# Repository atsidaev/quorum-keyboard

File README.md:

# Мини-клавиатура для Кворум-128

Пленка в клавиатуре Кворума-128 не очень прочна и много у кого уже умерла. На правах костыля можно заменить такую клавиатуру
на текстолитовый суррогат. Для установки требуется выпаять оргинальные разъемы и заменить их на штыри PLS.

# Mini-keyboard for Quorum-128 computer (Russian clone of ZX Spectrum)

Quorum-128 keyboard film is not very durable. But despite the Sinclair ZX Spectrum film, it cannot be simply bought on eBay.
So more radical solution is required.

This repo contains KiCad sources for very small repalcement keyboard. To install it one should replace film connector with
PLS pins.

## Explanation and soldering video

## Photos

## Gerbers

See Releases tab. 
[Latest version](https://github.com/atsidaev/quorum_keyboard/releases/download/v1.0/quorum-keyboard.zip)

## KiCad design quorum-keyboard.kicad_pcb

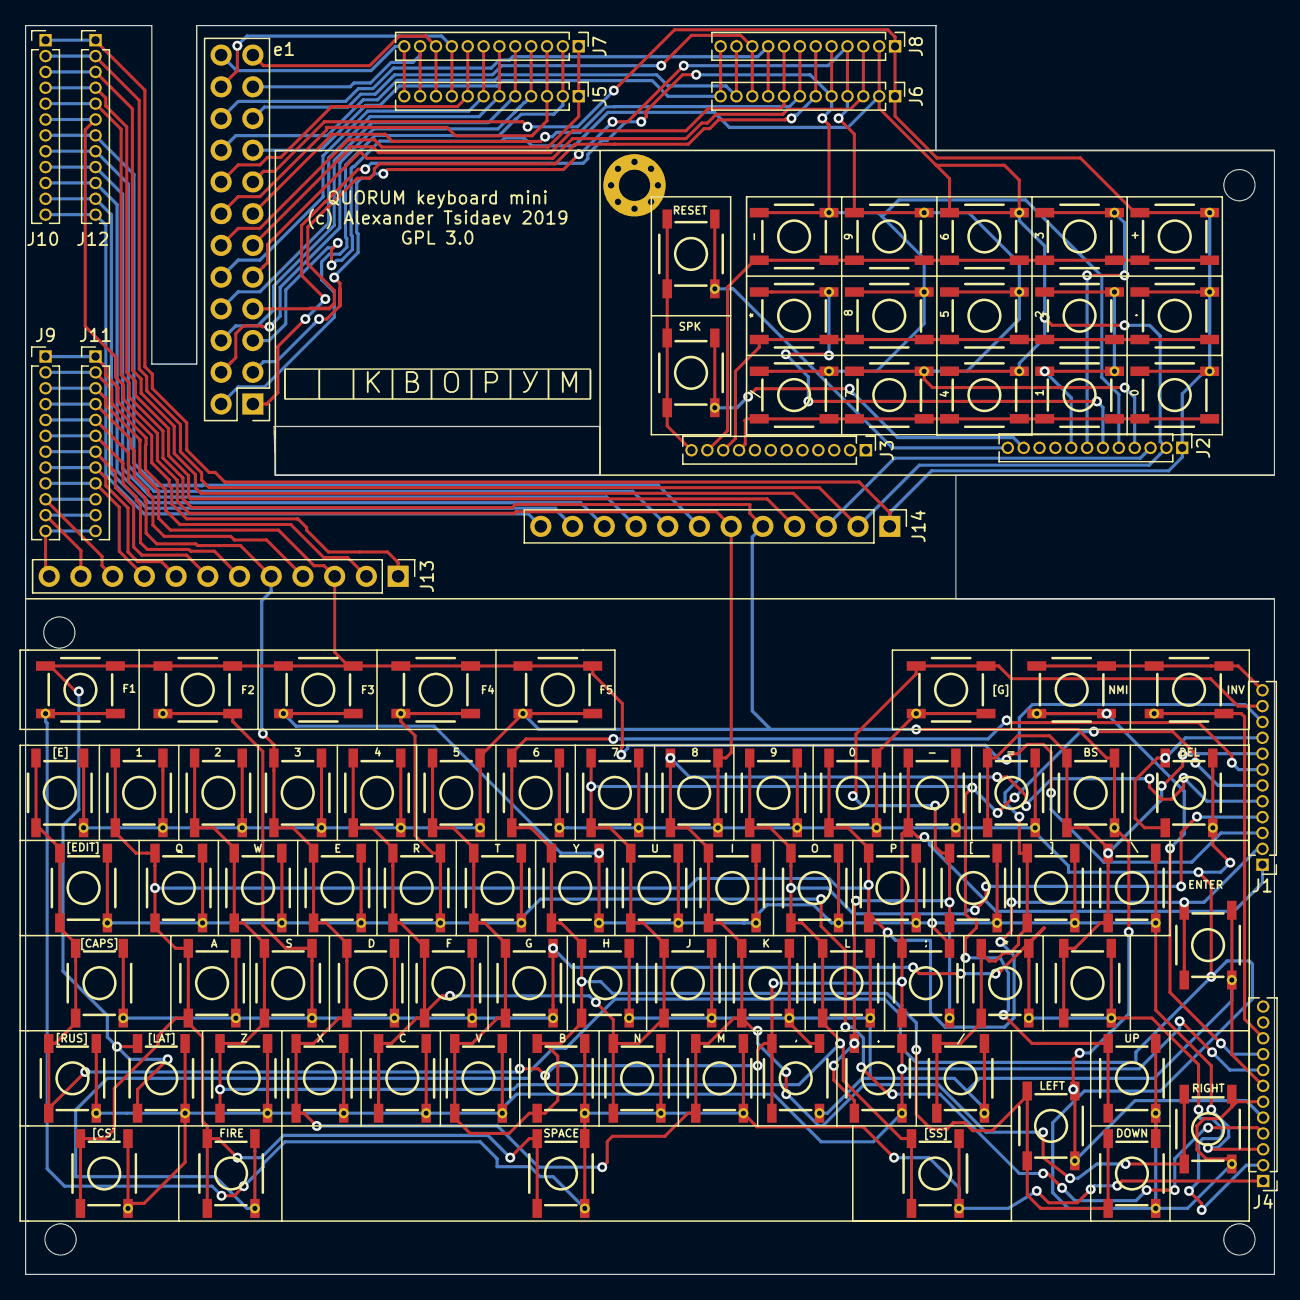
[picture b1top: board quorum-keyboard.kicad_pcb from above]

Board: 2 copper layers, 100.0 x 100.0 mm, 107 parts (0 on the bottom side), 24 nets.

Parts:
0, 0#2, 1, 1#2, 2, 2#2, 3, 3#2, 4, 4#2, 5, 5#2, 6, 6#2, 7, 7#2, 8, 8#2, 9, 9#2, ., .#2: QKB_TACTILE_SWITCH_SMD_5.2MM
 : MountingHole_2.5mm
 #2,  #3: MountingHole_2.5mm
*: QKB_TACTILE_SWITCH_SMD_5.2MM
*#2: QKB_TACTILE_SWITCH_SMD_5.2MM
+: QKB_TACTILE_SWITCH_SMD_5.2MM
,: QKB_TACTILE_SWITCH_SMD_5.2MM
-: QKB_TACTILE_SWITCH_SMD_5.2MM
-#2: QKB_TACTILE_SWITCH_SMD_5.2MM
/: QKB_TACTILE_SWITCH_SMD_5.2MM
/#2: QKB_TACTILE_SWITCH_SMD_5.2MM
;: QKB_TACTILE_SWITCH_SMD_5.2MM
=: QKB_TACTILE_SWITCH_SMD_5.2MM
A: QKB_TACTILE_SWITCH_SMD_5.2MM
B: QKB_TACTILE_SWITCH_SMD_5.2MM
BS: QKB_TACTILE_SWITCH_SMD_5.2MM
C: QKB_TACTILE_SWITCH_SMD_5.2MM
D: QKB_TACTILE_SWITCH_SMD_5.2MM
DEL: QKB_TACTILE_SWITCH_SMD_5.2MM
DOWN: QKB_TACTILE_SWITCH_SMD_5.2MM
E: QKB_TACTILE_SWITCH_SMD_5.2MM
ENTER: QKB_TACTILE_SWITCH_SMD_5.2MM
F, F1, F2, F3, F4, F5: QKB_TACTILE_SWITCH_SMD_5.2MM
FIRE: QKB_TACTILE_SWITCH_SMD_5.2MM
G: QKB_TACTILE_SWITCH_SMD_5.2MM
H: QKB_TACTILE_SWITCH_SMD_5.2MM
H3: MountingHole_2.5mm
H4: MountingHole_2.5mm_Pad_Via
I: QKB_TACTILE_SWITCH_SMD_5.2MM
INV: QKB_TACTILE_SWITCH_SMD_5.2MM
J: QKB_TACTILE_SWITCH_SMD_5.2MM
J1, J2, J3, J4, J5, J6, J7, J8, J9, J10, J11, J12: Pin_Header_Straight_1x12_Pitch1.27mm
J13, J14: Pin_Header_Straight_1x12_Pitch2.54mm
K: QKB_TACTILE_SWITCH_SMD_5.2MM
L: QKB_TACTILE_SWITCH_SMD_5.2MM
LEFT: QKB_TACTILE_SWITCH_SMD_5.2MM
M: QKB_TACTILE_SWITCH_SMD_5.2MM
N: QKB_TACTILE_SWITCH_SMD_5.2MM
NMI: QKB_TACTILE_SWITCH_SMD_5.2MM
O: QKB_TACTILE_SWITCH_SMD_5.2MM
P: QKB_TACTILE_SWITCH_SMD_5.2MM
Q: QKB_TACTILE_SWITCH_SMD_5.2MM
R: QKB_TACTILE_SWITCH_SMD_5.2MM
RESET: QKB_TACTILE_SWITCH_SMD_5.2MM
RIGHT: QKB_TACTILE_SWITCH_SMD_5.2MM
S: QKB_TACTILE_SWITCH_SMD_5.2MM
SPACE: QKB_TACTILE_SWITCH_SMD_5.2MM
SPK: QKB_TACTILE_SWITCH_SMD_5.2MM
T: QKB_TACTILE_SWITCH_SMD_5.2MM
U: QKB_TACTILE_SWITCH_SMD_5.2MM
UP: QKB_TACTILE_SWITCH_SMD_5.2MM
V: QKB_TACTILE_SWITCH_SMD_5.2MM
W: QKB_TACTILE_SWITCH_SMD_5.2MM
X: QKB_TACTILE_SWITCH_SMD_5.2MM
Y: QKB_TACTILE_SWITCH_SMD_5.2MM
Z: QKB_TACTILE_SWITCH_SMD_5.2MM
[: QKB_TACTILE_SWITCH_SMD_5.2MM
[CAPS]: QKB_TACTILE_SWITCH_SMD_5.2MM
[CS]: QKB_TACTILE_SWITCH_SMD_5.2MM
[EDIT]: QKB_TACTILE_SWITCH_SMD_5.2MM
[E]: QKB_TACTILE_SWITCH_SMD_5.2MM
[G]: QKB_TACTILE_SWITCH_SMD_5.2MM
[LAT]: QKB_TACTILE_SWITCH_SMD_5.2MM
[RUS]: QKB_TACTILE_SWITCH_SMD_5.2MM
[SS]: QKB_TACTILE_SWITCH_SMD_5.2MM
\: QKB_TACTILE_SWITCH_SMD_5.2MM
]: QKB_TACTILE_SWITCH_SMD_5.2MM
e1: Pin_Header_Straight_2x12_Pitch2.54mm

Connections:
A8: 1.3, 1.4, 2.3, 2.4, .#2.3, .#2.4, C.3, C.4, J2.8, J4.8, J6.8, J8.8, J10.8, J12.8, J14.8, V.3, V.4, X.3, X.4, Z.3, Z.4, [CS].3, [CS].4, [LAT].3, [LAT].4, [RUS].3, [RUS].4, e1.11
A9: 4.3, 4.4, 6.3, 6.4, *#2.3, *#2.4, A.3, A.4, D.3, D.4, F.3, F.4, F2.3, F2.4, G.3, G.4, J2.2, J4.2, J6.2, J8.2, J10.2, J12.2, J14.2, S.3, S.4, [CAPS].3, [CAPS].4, e1.5
A10: 5.3, 5.4, 7.3, 7.4, 9.3, 9.4, E.3, E.4, F4.3, F4.4, J2.4, J4.4, J6.4, J8.4, J10.4, J12.4, J14.4, Q.3, Q.4, R.3, R.4, T.3, T.4, W.3, W.4, [EDIT].3, [EDIT].4, e1.3
A11: 1#2.3, 1#2.4, 2#2.3, 2#2.4, 3#2.3, 3#2.4, 4#2.3, 4#2.4, 5#2.3, 5#2.4, 8.3, 8.4, -.3, -.4, /.3, /.4, BS.3, BS.4, F5.3, F5.4, J2.5, J4.5, J6.5, J8.5, J10.5, J12.5, J14.5, LEFT.3, LEFT.4, [E].3, [E].4, e1.1
A12: 0#2.3, 0#2.4, 6#2.3, 6#2.4, 7#2.3, 7#2.4, 8#2.3, 8#2.4, 9#2.3, 9#2.4, *.3, *.4, -#2.3, -#2.4, =.3, =.4, DEL.3, DEL.4, DOWN.3, DOWN.4, FIRE.3, FIRE.4, J2.6, J4.6, J6.6, J8.6, J10.6, J12.6, J14.6, RIGHT.3, RIGHT.4, UP.3, UP.4, [G].3, [G].4, e1.7
A13: ;.3, ;.4, F3.3, F3.4, I.3, I.4, J2.3, J4.3, J6.3, J8.3, J10.3, J12.3, J14.3, O.3, O.4, P.3, P.4, U.3, U.4, Y.3, Y.4, [.3, [.4, \.3, \.4, ].3, ].4, e1.9
A14: 3.3, 3.4, ,.3, ,.4, /#2.3, /#2.4, ENTER.3, ENTER.4, H.3, H.4, J.3, J.4, J2.7, J4.7, J6.7, J8.7, J10.7, J12.7, J14.7, K.3, K.4, L.3, L.4, e1.13
A15: 0.3, 0.4, +.3, +.4, ..3, ..4, B.3, B.4, F1.3, F1.4, J2.1, J4.1, J6.1, J8.1, J10.1, J12.1, J14.1, M.3, M.4, N.3, N.4, SPACE.3, SPACE.4, [SS].3, [SS].4, e1.15
D0: 0#2.1, 0#2.2, 1#2.1, 1#2.2, A.1, A.2, ENTER.1, ENTER.2, FIRE.1, FIRE.2, J1.2, J3.2, J5.2, J7.2, J9.2, J11.2, J13.2, P.1, P.2, Q.1, Q.2, SPACE.1, SPACE.2, [CS].1, [CS].2, e1.2
D0*: ,.1, ,.2, -#2.1, -#2.2, ;.1, ;.2, J1.1, J3.1, J5.1, J7.1, J9.1, J11.1, J13.1, [CAPS].1, [CAPS].2, [EDIT].1, [EDIT].2, [E].1, [E].2, [RUS].1, [RUS].2, e1.12
D1: 2#2.1, 2#2.2, 9#2.1, 9#2.2, J1.4, J3.4, J5.4, J7.4, J9.4, J11.4, J13.4, L.1, L.2, O.1, O.2, S.1, S.2, W.1, W.2, Z.1, Z.2, [SS].1, [SS].2, e1.4
D1*: F1.1, F1.2, F2.1, F2.2, F3.1, F3.2, F4.1, F4.2, F5.1, F5.2, J1.3, J3.3, J5.3, J7.3, J9.3, J11.3, J13.3, [LAT].1, [LAT].2, e1.14
D2: 3#2.1, 3#2.2, 8#2.1, 8#2.2, D.1, D.2, E.1, E.2, I.1, I.2, J1.5, J3.5, J5.5, J7.5, J9.5, J11.5, J13.5, K.1, K.2, M.1, M.2, RIGHT.1, RIGHT.2, X.1, X.2, e1.6
D2*: =.1, =.2, BS.1, BS.2, J1.8, J3.8, J5.8, J7.8, J9.8, J11.8, J13.8, \.1, \.2, e1.16
D3: 4#2.1, 4#2.2, 7#2.1, 7#2.2, C.1, C.2, F.1, F.2, J.1, J.2, J1.6, J3.6, J5.6, J7.6, J9.6, J11.6, J13.6, N.1, N.2, R.1, R.2, U.1, U.2, UP.1, UP.2, e1.8
D3*: 0.1, 0.2, 1.1, 1.2, 4.1, 4.2, 7.1, 7.2, /.1, /.2, DEL.1, DEL.2, J1.9, J3.9, J5.9, J7.9, J9.9, J11.9, J13.9, e1.22
D4: 5#2.1, 5#2.2, 6#2.1, 6#2.2, B.1, B.2, DOWN.1, DOWN.2, G.1, G.2, H.1, H.2, J1.7, J3.7, J5.7, J7.7, J9.7, J11.7, J13.7, LEFT.1, LEFT.2, T.1, T.2, V.1, V.2, Y.1, Y.2, e1.10
D4*: 2.1, 2.2, 5.1, 5.2, 8.1, 8.2, *.1, *.2, *#2.1, *#2.2, ..1, ..2, /#2.1, /#2.2, J1.10, J3.10, J5.10, J7.10, J9.10, J11.10, J13.10, ].1, ].2, e1.23
D5*: 3.1, 3.2, 6.1, 6.2, 9.1, 9.2, +.1, +.2, -.1, -.2, .#2.1, .#2.2, J1.11, J3.11, J5.11, J7.11, J9.11, J11.11, J13.11, [.1, [.2, [G].1, [G].2, e1.21
GND: INV.1, INV.2, J1.12, J3.12, J5.12, J7.12, J9.12, J11.12, J13.12, NMI.1, NMI.2, RESET.1, RESET.2, SPK.1, SPK.2, e1.24
KINV: INV.3, INV.4, J2.10, J4.10, J6.10, J8.10, J10.10, J12.10, J14.10, e1.19
KNMI: J2.9, J4.9, J6.9, J8.9, J10.9, J12.9, J14.9, NMI.3, NMI.4, e1.20
KSPC: J2.11, J4.11, J6.11, J8.11, J10.11, J12.11, J14.11, SPK.3, SPK.4, e1.18
RES: J2.12, J4.12, J6.12, J8.12, J10.12, J12.12, J14.12, RESET.3, RESET.4, e1.17

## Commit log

2019-11-14 Initial
2020-05-05 Silkscreen added. No mask on pads at boards contact.
2020-05-11 Tactile switch model .gitignore updated
2020-05-11 Create LICENSE

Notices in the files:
quorum-keyboard.kicad_pcb:
GPL 3.0
